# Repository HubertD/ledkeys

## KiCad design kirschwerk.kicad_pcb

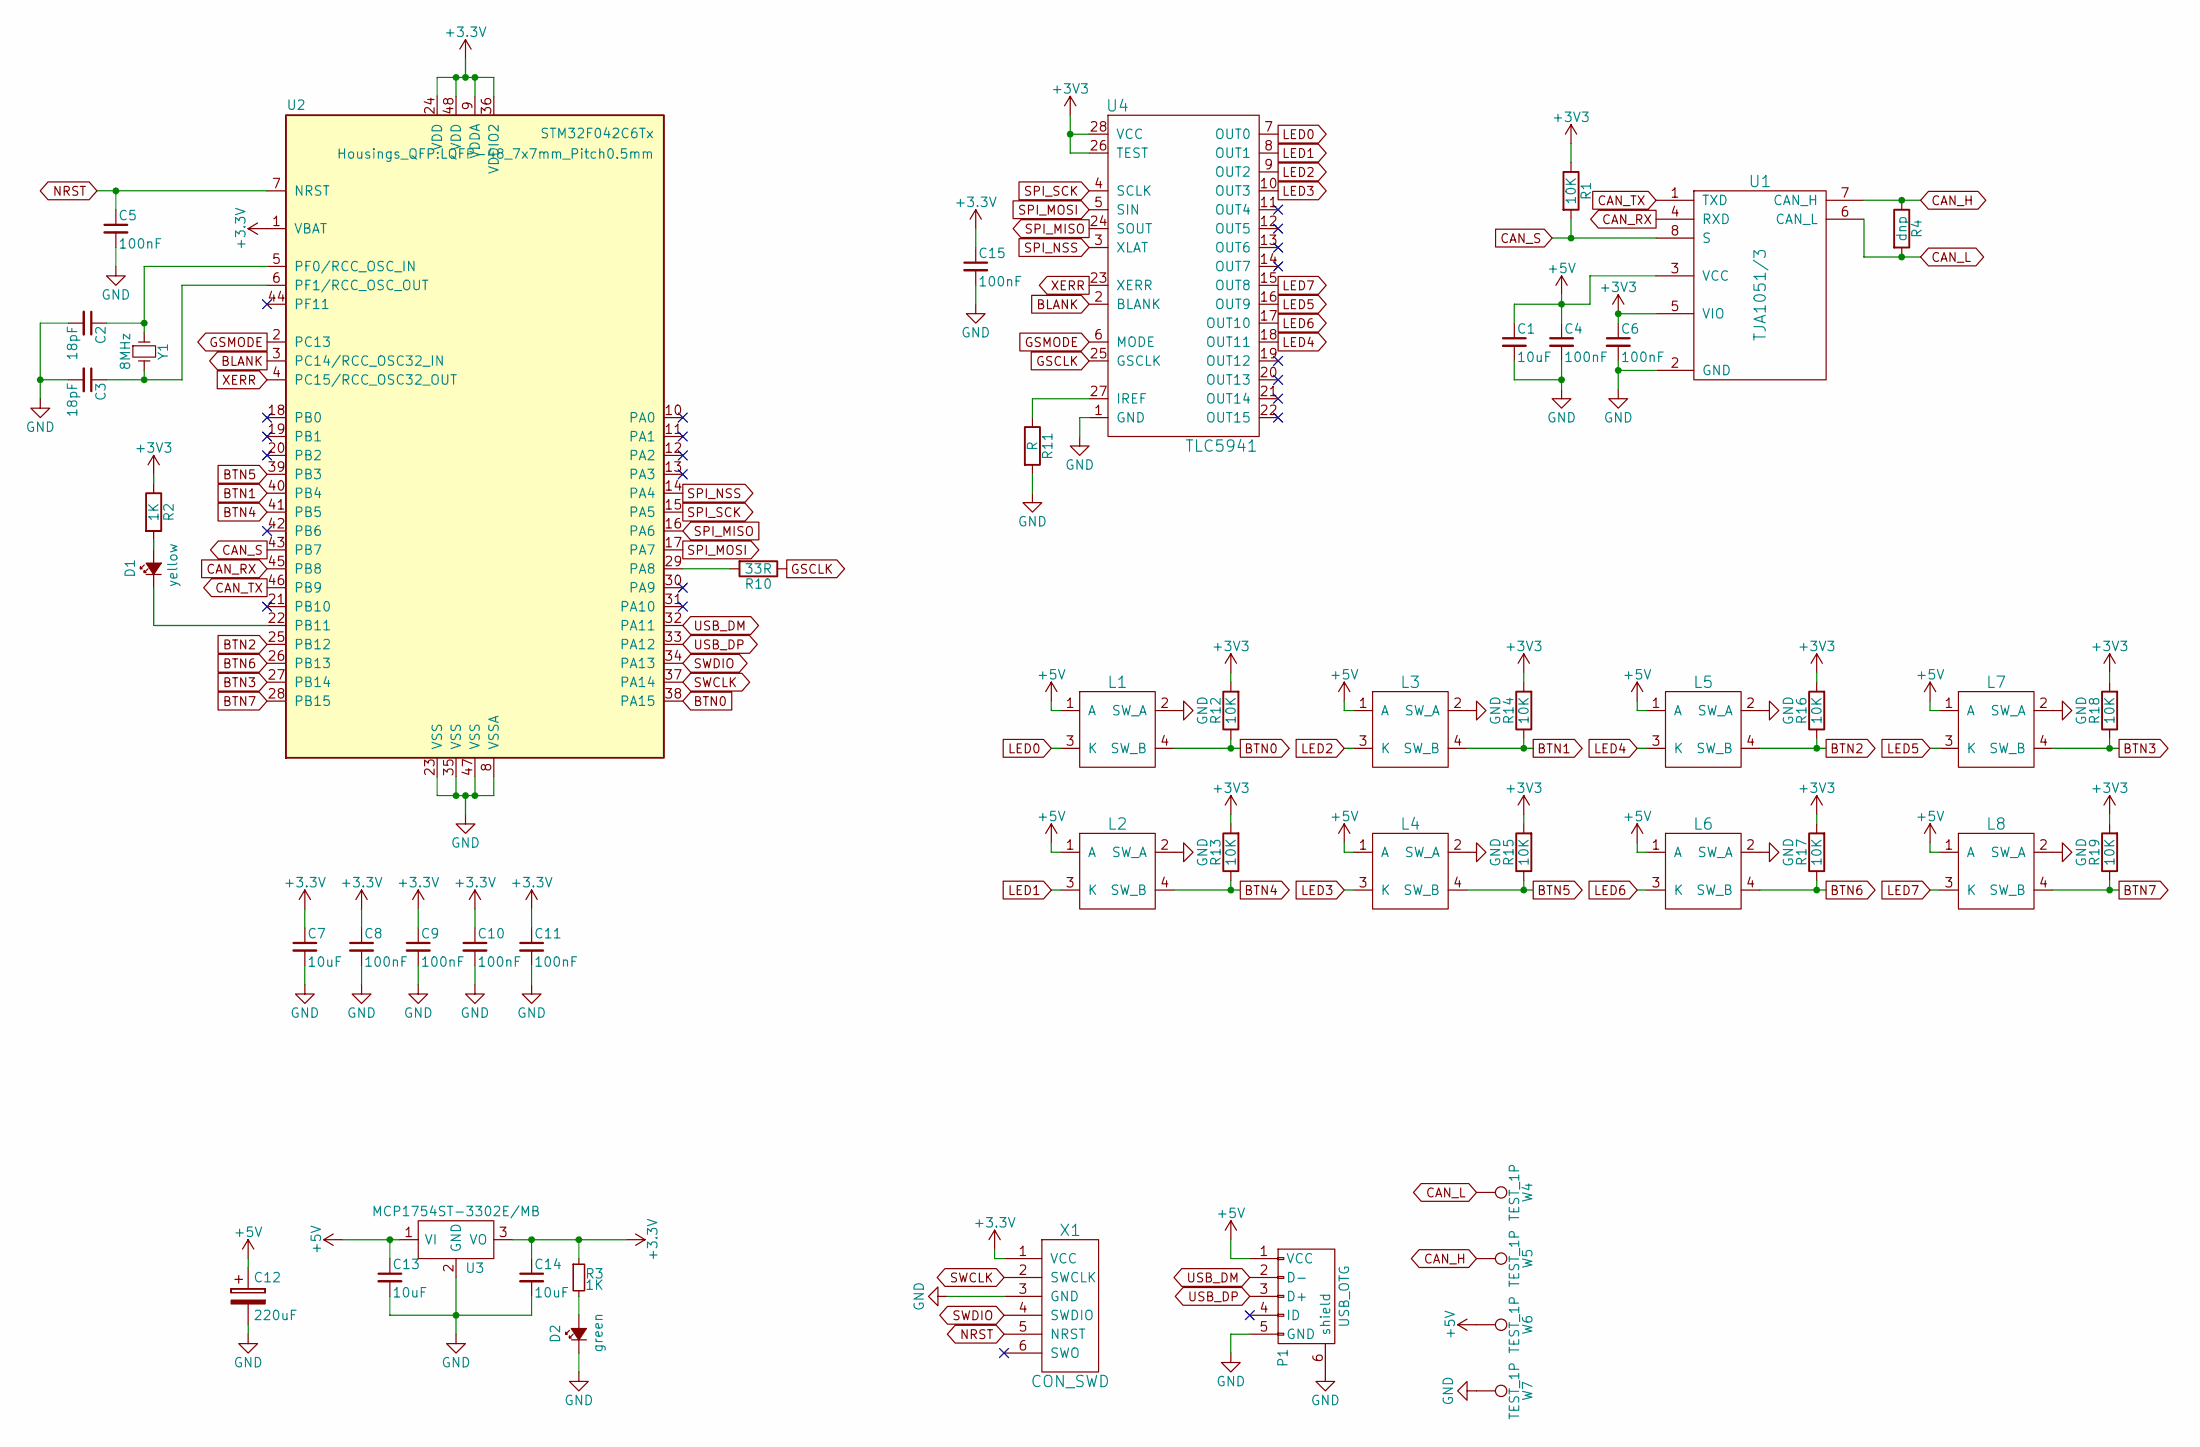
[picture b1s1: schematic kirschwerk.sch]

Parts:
C1, C7, C13, C14: 10uF; C_0805
C2, C3: 18pF; C_0603
C4, C5, C6, C8, C9, C10, C11, C15: 100nF; C_0603
C12: 220uF; TantalC_SizeD_EIA-7343_Reflow
D1: yellow; LED_0603
D2: green; LED_0603
L1, L2, L3, L4, L5, L6, L7, L8: marquardt-3006; marquard-3006
P1: USB_OTG; Molex-Micro-USB-B-Middle-Mount
R1, R12, R13, R14, R15, R16, R17, R18, R19: 10K; R_0603
R2, R3: 1K; R_0603
R4: dnp; R_0603
R10: 33R; R_0603
R11: R; R_0603
U1: TJA1051/3; SOIC-8_3.9x4.9mm_Pitch1.27mm
U2: STM32F042C6Tx; LQFP-48_7x7mm_Pitch0.5mm
U3: MCP1754ST-3302E/MB; SOT89-3_Housing
U4: TLC5941; TSSOP-28_4.4x9.7mm_Pitch0.65mm
W4, W5, W6, W7: TEST_1P; Measurement_Point_Square-SMD-Pad_Big
X1: CON_SWD; TC2030-NL
Y1: 8MHz; ABM3

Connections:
+5V: C1.1, C4.1, C12.1, C13.1, L1.1 (A), L2.1 (A), L3.1 (A), L4.1 (A), L5.1 (A), L6.1 (A), L7.1 (A), L8.1 (A), P1.1 (VCC), U1.3 (VCC), U3.1 (VI), W6.1
BLANK: U2.3 (PC14/RCC_OSC32_IN), U4.2 (BLANK)
BTN0: L1.4 (SW_B), R12.1, U2.38 (PA15)
BTN1: L3.4 (SW_B), R14.1, U2.40 (PB4)
BTN2: L5.4 (SW_B), R16.1, U2.25 (PB12)
BTN3: L7.4 (SW_B), R18.1, U2.27 (PB14)
BTN4: L2.4 (SW_B), R13.1, U2.41 (PB5)
BTN5: L4.4 (SW_B), R15.1, U2.39 (PB3)
BTN6: L6.4 (SW_B), R17.1, U2.26 (PB13)
BTN7: L8.4 (SW_B), R19.1, U2.28 (PB15)
CAN_H: R4.1, U1.7 (CAN_H), W5.1
CAN_L: R4.2, U1.6 (CAN_L), W4.1
CAN_RX: U1.4 (RXD), U2.45 (PB8)
CAN_S: R1.2, U1.8 (S), U2.43 (PB7)
CAN_TX: U1.1 (TXD), U2.46 (PB9)
GND: C1.2, C2.2, C3.2, C4.2, C5.2, C6.2, C7.2, C8.2, C9.2, C10.2, C11.2, C12.2, C13.2, C14.2, C15.2, D2.1 (K), L1.2 (SW_A), L2.2 (SW_A), L3.2 (SW_A), L4.2 (SW_A), L5.2 (SW_A), L6.2 (SW_A), L7.2 (SW_A), L8.2 (SW_A), P1.5 (GND), P1.6 (shield), R11.2, U1.2 (GND), U2.8 (VSSA), U2.23 (VSS), U2.35 (VSS), U2.47 (VSS), U3.2 (GND), U4.1 (GND), W7.1, X1.3 (GND)
GSCLK: R10.1, U4.25 (GSCLK)
GSMODE: U2.2 (PC13), U4.6 (MODE)
LED0: L1.3 (K), U4.7 (OUT0)
LED1: L2.3 (K), U4.8 (OUT1)
LED2: L3.3 (K), U4.9 (OUT2)
LED3: L4.3 (K), U4.10 (OUT3)
LED4: L5.3 (K), U4.18 (OUT11)
LED5: L7.3 (K), U4.16 (OUT9)
LED6: L6.3 (K), U4.17 (OUT10)
LED7: L8.3 (K), U4.15 (OUT8)
NRST: C5.1, U2.7 (NRST), X1.5 (NRST)
unnamed: C2.1, U2.5 (PF0/RCC_OSC_IN), Y1.1
unnamed: C3.1, U2.6 (PF1/RCC_OSC_OUT), Y1.2
unnamed: D1.1 (K), U2.22 (PB11)
unnamed: D1.2 (A), R2.2
unnamed: D2.2 (A), R3.2
unnamed: R10.2, U2.29 (PA8)
unnamed: R11.1, U4.27 (IREF)
SPI_MISO: U2.16 (PA6), U4.24 (SOUT)
SPI_MOSI: U2.17 (PA7), U4.5 (SIN)
SPI_NSS: U2.14 (PA4), U4.3 (XLAT)
SPI_SCK: U2.15 (PA5), U4.4 (SCLK)
SWCLK: U2.37 (PA14), X1.2 (SWCLK)
SWDIO: U2.34 (PA13), X1.4 (SWDIO)
USB_DM: P1.2 (D-), U2.32 (PA11)
USB_DP: P1.3 (D+), U2.33 (PA12)
XERR: U2.4 (PC15/RCC_OSC32_OUT), U4.23 (XERR)

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
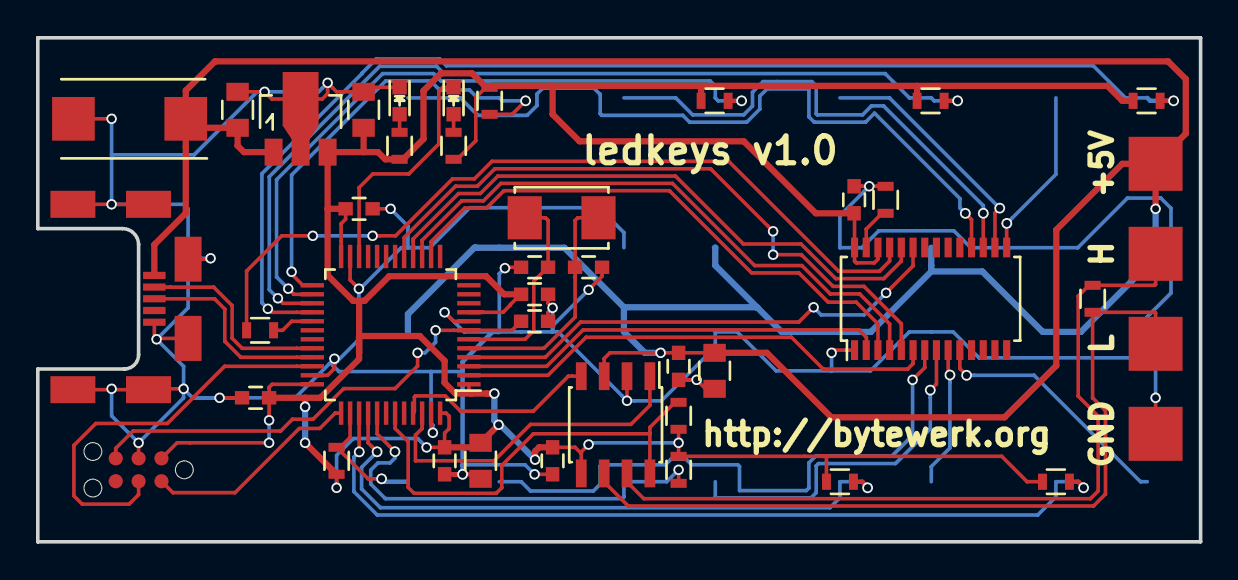
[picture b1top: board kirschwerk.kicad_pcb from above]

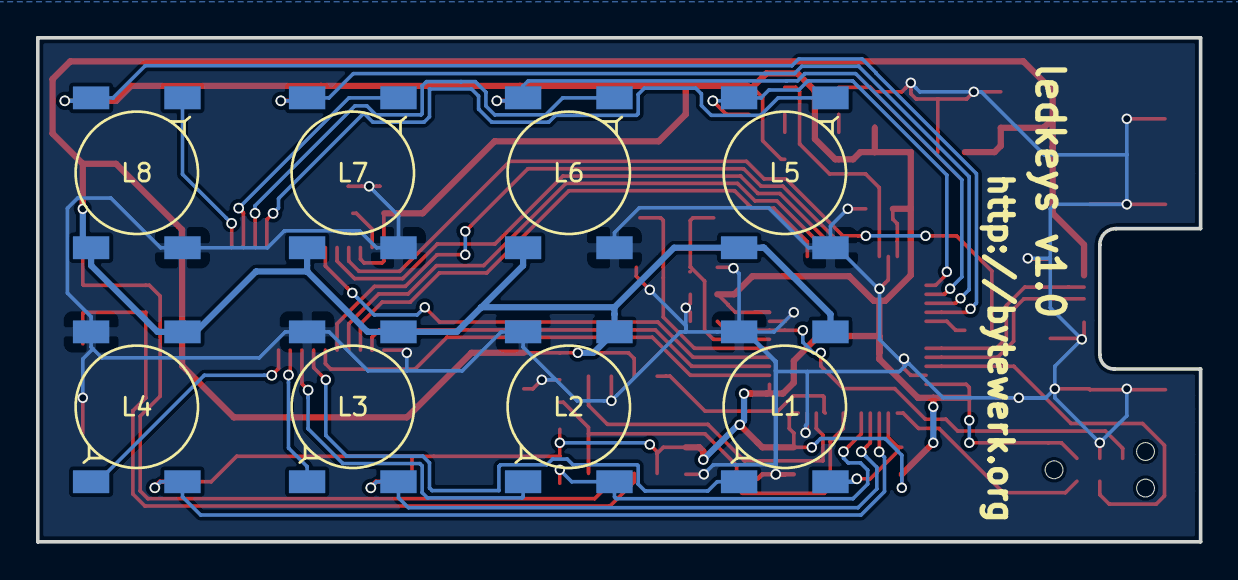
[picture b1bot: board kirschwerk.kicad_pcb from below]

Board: 2 copper layers, 64.6 x 28.0 mm, 50 parts (8 on the bottom side), 44 nets.

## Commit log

2016-06-24 initial checkin
2016-06-24 a4 is enough
